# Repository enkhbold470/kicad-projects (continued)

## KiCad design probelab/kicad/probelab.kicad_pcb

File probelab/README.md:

# ProbeLab

An RP2040 USB-C logic analyzer: 16 buffered 5 V-tolerant inputs plus two low-speed scope channels.

| Layers | Size | Parts | Nets | Connections routed | Vias | ERC errors | DRC errors / unconnected / parity |
|---|---|---|---|---|---|---|---|
| 4 | 58 x 70 mm | 88 | 84 | 253 -> 0 open | 171 | 0 | 0 / 0 / 0 |

**Not fabricated, assembled or powered.** Every number on this page is measured by KiCad 10 on the files in this folder; the full measurements are in [`report.json`](report.json).

| | |
|---|---|
| KiCad project | [`kicad/`](kicad/) |
| Gerbers, BOM, CPL, STEP, schematic PDF | [`fab/`](fab/) |
| Renders | [top](media/top.png), [bottom](media/bottom.png) |
| Design process, every step as KiCad rendered it | [`media/design-process.mp4`](media/design-process.mp4) |

ProbeLab is a USB-C logic analyzer meant for sigrok/PulseView with sigrok-pico-style RP2040 firmware. It has 16 buffered and clamped logic inputs and two low-speed scope channels into the RP2040's own ADC, on a 58 x 70 mm, 4-layer board.

It was designed with the HeyPCB method on KiCad 10 (10.0.6), headless. A hand-written brief (`board.json`) is composed from reusable circuit blocks, and one pipeline run then does the schematic, ERC, a netlist round trip, placement, routing with Freerouting 2.4.1, pours and stitching, DRC with schematic parity, a fab gate, the fab outputs, 3D renders and a video. In the heypcb-kicad repository, `./run.sh --board boards/probelab` rebuilds all of it from `board.json`.

**Status: not fabricated, assembled or powered.** The final run passes every gate it has: ERC, the netlist round trip, routing to 0 open, DRC with schematic parity, DFM and the fab gate. That shows the design files agree with each other and with the fab's rules. It does not show that the circuit works.

**Limits.** The scope channels are low speed: they use the RP2040's ADC, 500 kS/s (datasheet) shared between the enabled channels. The logic inputs read 3.3 V and 5 V logic. 1.8 V logic sits below the buffer's 2.0 V VIH and will not read reliably.

**Firmware is separate.** Nothing here contains or tests firmware. The GPIO map below is what a firmware build has to match, and compatibility with sigrok-pico has not been checked on hardware.

## Files

| Path | Contents |
|---|---|
| `board.json` | the brief the pipeline built from |
| `report.json` | the run's measurements; every gate number below comes from it |
| `kicad/` | `probelab.kicad_pro`, `probelab.kicad_sch`, `probelab.kicad_pcb`. `models/` holds a simplified body for the USB-C receptacle, because KiCad 10 ships no 3D model for the HRO TYPE-C-31-M-12. It is not the vendor model |
| `fab/probelab_gerbers.zip` | 4 copper layers, mask, paste, silkscreen, outline, drill and drill map, gerber job |
| `fab/probelab_bom.csv` | 32 lines, 84 parts, each with an LCSC number |
| `fab/probelab_cpl_jlc.csv`, `fab/probelab_pos.csv` | placement for the 81 SMD parts (the through-hole headers are not in them) |
| `fab/probelab_schematic.pdf`, `fab/probelab.step` | schematic and 3D model |
| `media/` | board images and the run recorded stage by stage (`design-process.gif`, `design-process.mp4`) |

## Specs

- **MCU:** RP2040 with a 12 MHz Abracon ABM8-272-T3 crystal (CL 10 pF; 15 pF load caps, 1k on XOUT), the way Raspberry Pi's minimal design wires it.
- **Flash:** W25Q128JVSIQ, 16 MB, QSPI.
- **Core supply:** the RP2040's on-chip regulator makes the 1.1 V core (VREG_VOUT to both DVDD pins, 1 uF at each end of the regulator).
- **Decoupling:** 100 nF on every IOVDD, DVDD, USB_VDD and ADC_AVDD pin and 1 uF on VREG_VIN and VREG_VOUT, all 0402, all on the top side within 2.3 mm of the pin each one serves, each joined to it on F.Cu with no via (measured, see below).
- **USB:** USB-C receptacle (HRO TYPE-C-31-M-12) with 5.1k CC pull-downs, a USBLC6-2SC6 ESD clamp, and 27R in series with D+/D-.
- **Power:** AP2112K-3.3 LDO from VBUS. The draw is expected to stay well under 150 mA. That is an estimate; nothing has been powered.
- **Logic inputs (16, D0-D15):**
  - two 2x10 0.1" headers, signals on the even pins, ground on every odd pin and on pins 18/20;
  - each line clamped at the header by a USBLC6-4SC6 (rail pin on VBUS, so 5 V logic passes);
  - then 100R in series into an SN74LVC245A powered at 3.3 V, fixed A to B (DIR high, OE low), which drives GPIO2-GPIO17;
  - inputs are 5 V tolerant, with thresholds VIH 2.0 V / VIL 0.8 V.
- **Scope inputs (2):** a 1x4 header (CH1, GND, CH2, GND). Each channel has:
  - a PCM12 AC/DC slide switch shorting a 100 nF coupling cap (AC corner about 1.4 Hz);
  - 1M into a node held at mid-rail by 220k/220k, so Vnode = 0.099 x Vin + 1.49 V and about -15 V to +18 V spans 0-3.3 V, with about 1.1 Mohm input resistance;
  - a TLV9061 rail-to-rail buffer, then 47R + 1 nF into the ADC pin.
  - CH1 goes to ADC0 (GPIO26) and CH2 to ADC1 (GPIO27).
- **UI:** BOOT button (QSPI_SS through 1k), RESET button (RUN, 10k pull-up), and three LEDs: PWR (green, 3V3), STAT (GPIO25) and ACT (GPIO24).
- **Board:** 58 x 70 mm with 2 mm corner radii, 4 copper layers (below), every part on the top side. Four M3 holes, each 3.50 mm in from both edges at its corner: a 51 x 63 mm pattern centred on the board. 88 footprints: 84 populated parts and the 4 holes.
- **Silkscreen:** D0-D15 and the two all-ground rows of each header (pins 17-20) are named on both faces, CH1/GND/CH2/GND beside the scope header, BOOT, RST, USB, PWR, STAT and ACT beside their parts, DC and AC beside each switch's throws, and four title lines on the back (name, "16ch logic + 2ch scope", "RP2040 / sigrok", revision). The odd-pin grounds of the outer header column carry no label.

| Function | RP2040 pin(s) |
|---|---|
| D0-D7 (header J2, via U5) | GPIO2-GPIO9 |
| D8-D15 (header J3, via U8) | GPIO10-GPIO17 |
| Scope CH1 / CH2 | GPIO26 (ADC0) / GPIO27 (ADC1) |
| STAT / ACT LED | GPIO25 / GPIO24 |
| BOOT / RESET | QSPI_SS via 1k / RUN |
| Not connected | GPIO0-1, GPIO18-23, GPIO28-29, SWCLK, SWDIO |

## RP2040 decoupling, measured

Read off the final `kicad/probelab.kicad_pcb` with KiCad's Python (`pcbnew`). *Pad to pin* is the distance from the centre of the cap's supply pad (pad 1) to the centre of the RP2040 pin it serves. *Track path* is the shortest run of copper track between the two pads, through vias if any; the 3V3 pour on In1 is not counted. *Before* is the same measurement on the previous build of this board, with the caps where the earlier brief put them.

| Cap | Pin | Supply | Value | Pad to pin | Track path | Before |
|---|---|---|---|---|---|---|
| C1 | 1 | IOVDD | 100 nF | 1.51 mm | 1.61 mm, F.Cu | 1.51 mm, 1.61 mm F.Cu |
| C2 | 10 | IOVDD | 100 nF | 1.63 mm | 1.63 mm, F.Cu | 5.31 mm, 7.68 mm F.Cu |
| C3 | 22 | IOVDD | 100 nF | 1.35 mm | 1.11 mm, F.Cu | 4.89 mm, 13.31 mm F.Cu |
| C4 | 33 | IOVDD | 100 nF | 1.23 mm | 1.23 mm, F.Cu | 2.25 mm, 2.63 mm F.Cu |
| C5 | 42 | IOVDD | 100 nF | 1.23 mm | 1.23 mm, F.Cu | 2.25 mm, 2.63 mm F.Cu |
| C6 | 49 | IOVDD | 100 nF | 1.24 mm | 1.40 mm, F.Cu | 1.34 mm, 1.23 mm F.Cu |
| C7 | 48 | USB_VDD | 100 nF | 2.02 mm | 2.73 mm, F.Cu | 7.74 mm, 23.77 mm through 2 vias |
| C8 | 43 | ADC_AVDD | 100 nF | 2.07 mm | 3.57 mm, F.Cu | 2.16 mm, 2.68 mm F.Cu |
| C9 | 44 | VREG_VIN | 1 uF | 2.24 mm | 5.23 mm, F.Cu | 1.67 mm, 1.98 mm F.Cu |
| C10 | 45 | VREG_VOUT | 1 uF | 1.76 mm | 2.04 mm, F.Cu | 1.37 mm, 1.46 mm F.Cu |
| C11 | 23 | DVDD | 100 nF | 1.58 mm | 1.68 mm, F.Cu | 4.96 mm, 7.29 mm F.Cu |
| C12 | 50 | DVDD | 100 nF | 1.87 mm | 2.00 mm, F.Cu | 9.17 mm, 16.33 mm through 3 vias |

- No cap is on the bottom side, and no cap reaches its pin through a via. A track path can come out shorter than the centre distance, because it is counted from where the track meets each pad.
- The top edge of the QFN carries pins 48-50 between the QSPI pins and the USB pair. The flash is turned (rotation 270 in the brief) so no QSPI line crosses the space above them. C6 sits straight over pins 49 and 48 (both 3V3), C12 up and left of pin 50, C7 up and right of pin 48. The cost is on the right of the USB pair: C10 and C9 moved 0.9 and 0.8 mm right to leave a 1.05 mm channel for the USB lines, so they are 0.39 and 0.57 mm farther from pins 45 and 44 than before.
- **C9's path is long.** Its pad is 2.24 mm from pin 44, but the router joined pins 43/44 to pin 42's cap C5 and the corner cap C8 and reached C9 from C8, so the shortest track from C9 to pin 44 runs 5.23 mm. C8's 3.57 mm path also runs through pin 42 and C5. Two variants of the brief that moved C10 0.1 and 0.2 mm up gave C9 5.12 and 4.33 mm, but cost C1 a 45 mm path through 3 vias or C10 a path through 2 vias, so they were not kept.
- On the left side, C2 sits level with pin 10 in the middle of the GPIO escape. The router takes GPIO6-9 (pins 8, 9, 11 and 12) past it through vias, two of them under the QFN body.
- The bottom pins 22 and 23 have their caps directly under them (C3, C11), right of the XOUT line. R1, the 1k on XOUT, moved 0.3 mm down to make room.

## Stackup and copper

Read off the final `kicad/probelab.kicad_pcb` with KiCad's Python (`pcbnew`); the track lengths and via counts match `report.json`.

| Layer | While routing | After routing | Tracks | Pour fill |
|---|---|---|---|---|
| F.Cu | signal | GND pour | 874.6 mm | 3023 mm² |
| In1.Cu | signal | 3V3 pour | 630.1 mm | 3194 mm² |
| In2.Cu | GND plane (a Specctra power layer, no tracks) | GND pour | none | 3630 mm² |
| B.Cu | signal | GND pour | 290.1 mm | 3440 mm² |

- `board.json` sets one plane, `In2.Cu: GND`. The brief has no `pours` key, so the 3V3 pour on In1 comes from the pipeline's 4-layer pour rule: when no plane carries a supply, the inner signal layer takes the dominant rail after routing. It covers In1's 3V3 tracks.
- 920 tracks, 1794.8 mm. VBUS is 0.4 mm except 6 segments (5.5 mm) at 0.3 mm. 72 segments (57.0 mm in all) are 0.15 mm: short pad exits from Freerouting's fanout solve on 33 nets, which the width floor could not widen without breaking a clearance. Every other track is 0.2 mm, including 3V3, 1V1 and USB D+/D-.
- 171 vias, all through vias of 0.6 mm with a 0.3 mm hole: 114 from routing and 57 GND stitching vias (the stitcher placed 63; the silk stage removed 6 under text).
- 10 of the routing vias sit under the RP2040's body, inside its ring of pins (6 on the previous build).
- `board.keepouts` holds one rule area, `pin_labels_D10_D15`: no vias on any layer in a 3 x 14.5 mm strip under the D10-D15 header labels.
- The gerber job gives four 35 µm copper layers, three 0.48 mm FR4 dielectrics, 1.6 mm overall. That is KiCad's default 4-layer stackup, not a fab's. Nothing on the board is impedance controlled.

## Choices and substitutions

- **The RP2040's own ADC instead of a fast external ADC.** The RP2040 has 30 GPIO, and 16 of them go to the logic inputs.
  - AD9288 (dual 8-bit) has no KiCad 10 symbol.
  - ADC08060 has a symbol, but it is one channel with 8 parallel data lines. Two of them need 16 data pins plus a clock, which does not fit beside 16 logic channels.
  - Two analog nets into GPIO26/27 is by far the most routable option. GPIO26-29 are the RP2040's only ADC pins, so any RP2040 capture firmware reads analog there.
  - The cost: RP2040 ADC bandwidth. Its 500 kS/s (datasheet) is shared between the enabled channels.
- **TLV9061 instead of AD8065 or OPA356.**
  - AD8065 has no KiCad 10 symbol and needs a supply above 3.3 V.
  - OPA356 has a symbol, but it is rail-to-rail on its output only. Its input range stops short of V+, so at 3.3 V it would clip a node biased to mid-rail.
  - TLV9061 is a single-channel SOT-23-5, rail to rail on input and output, 10 MHz, and in stock (C398358).
- **SN74LVC245A, not 74LVC8T245.** It needs one supply and no target-voltage selector. The trade-off: it reads 3.3 V and 5 V logic, but not 1.8 V logic reliably.
- **ABM8-272-T3 (Extended) instead of the Basic C9002 crystal.** C9002 is CL 20 pF. ABM8-272-T3 (CL 10 pF) is the crystal Raspberry Pi's minimal design uses, and 15 pF caps suit it.
- **GND plane on In2, not In1.** Measured on 2026-09-30, on the earlier 56 x 68 mm outline: with In1 as the Specctra power layer, Freerouting left the header ground pins open in every solve (23, 30 and 37 opens, all GND at J2/J3). With In2 as the power layer it closed them. That was before the pipeline started removing plane-layer shapes from through-hole pin padstacks for the router, a change aimed at the same kind of failure. In1 as the plane has not been re-tested since.
- **58 x 70 mm, not 56 x 68.** Once the router was held to the brief's 0.5 mm hole-to-hole spacing between vias, the 56 x 68 mm board left 1V1 open at U1 pin 50 (measured 2026-10-01). At 58 x 70 mm it routed to 0 open.
- **PWR class is VBUS only (0.4 mm).** 3V3 and 1V1 stay at the 0.2 mm default. A 0.3 mm class could not enter the RP2040's 0.2 mm QFN power pins with neckdown off (6 opens until the ladder narrowed it, measured 2026-09-30).
- **QFN-56 ThermalVias footprint.** The exposed pad is the RP2040's only ground pin. The plain footprint leaves it enclosed by 0.4 mm-pitch pins. The symbol's footprint filter allows this variant.
- **Every RP2040 passive is locked in the brief,** and the flash is its own block. Left to the shelf placer, every IOVDD cap landed around the flash (it prefers the IC with fewer pads on the rail). The locks put each supply cap beside its pin with pad 1 toward it. The USB channel between C7 and C10 is 1.05 mm. At 0.9 mm, the bare minimum for two 0.2 mm tracks, the first run of this placement routed every connection, but once the label keep-out was added the fanout solve left U1_DM_MCU open; at 1.05 mm it routes everything (measured 2026-10-01, one run each). Since the keep-out, the fanout-off solve has left VBUS (U7.5 to C16.1) open on every run.
- **The input clamps sit 1.8 mm farther from the headers than before** (pads from 10.0 mm), so the pin labels the silk stage sets inside each signal pad fit on the front. A via-free strip (`board.keepouts`) under the D10-D15 labels keeps router vias off them; without it, two router vias left D10 and D14 unlabelled on both faces.
- **The coupling cap of each scope channel is locked between its switch's input and common rows,** clear of the DC and AC words beside pads 1 and 3. Placed by the shelf placer, it sat where the DC word goes.

New blocks, all prefixed `probe_`:
- `probe_rp2040_core`
- `probe_qspi_flash`
- `probe_logic_bank8`
- `probe_scope_frontend`
- `probe_header_1x04`
- `probe_mounting_holes_m3`

Reused blocks:
- `usb_c_data_5v`
- `usb_esd_usblc6`
- `lipo_ldo_ap2112k` (VBAT renamed onto VBUS)
- `tactile_button`
- `led_indicator`
- `gpio_led`

## Measured gates

The final run, 2026-10-01, with media. Every number is from `report.json`, except the block counts, which are counted in `board.json`.

| Gate | Result |
|---|---|
| Composition | 16 block instances, 12 distinct blocks: 88 parts, 84 nets, 16 no-connect pins |
| Part binding | 84 of 84 populated parts bound to LCSC numbers; the 4 mounting holes are DNP and not in the BOM. 0 unsourced, 0 identity conflicts. 14 distinct Extended parts, about $42 in JLC loading fees |
| ERC (`--severity-all`) | 0 errors, 0 warnings |
| Netlist round trip | identical, 84 nets |
| Placement | 44 parts locked by the brief, 3 edge parts (USB-C, both AC/DC switches), 3 LED-block anchors at brief targets, 38 placed by the shelf placer around the pins they serve |
| Routing | 253 connections, two rung-1 Freerouting solves. **Fanout on: 0 open** in 20.0 s with 114 vias. This solve is kept. Fanout off: 1 open (VBUS, U7.5 to C16.1) in 47.4 s with 78 vias; the last-mile router found no path for it |
| Copper | 920 tracks, 1794.8 mm (F.Cu 874.6, In1.Cu 630.1, B.Cu 290.1) |
| Pours (after a measured 0 open) | GND on F.Cu, B.Cu and In2.Cu, 3V3 on In1.Cu. 63 stitching vias placed, 177 vias in all before the silk stage. 0 open after the pours, after stitching and at the end |
| DRC (`--severity-all --schematic-parity`) | fresh: 0 errors, 0 unconnected, **0 parity issues**, 4 warnings: 3 `lib_footprint_mismatch`, 1 `hole_to_hole` |
| DFM (`jlcpcb_4layer`) | 0 errors, 1 warning: 262 stock-footprint silk strokes at 0.12 mm, which the fab prints at its 0.15 mm minimum |
| Fab gate | **ready**, no blockers. 4 copper gerbers and a gerber job with LayerNumber 4, drill, BOM, CPL (11 rotations corrected), position file, schematic PDF, STEP |
| Silkscreen | 48 header pin labels, 10 words, 57 designators seated, 23 hidden, 13 footprint silk items clipped at the board edge, 4 of 4 back-side title lines placed (as one block, 10 mm left of the brief's spot), 6 stitching vias removed under text |
| Media | 63 3D frames, the raytraced renders and the design-process video all ran; the video is 219 stills at 1920 x 1080, 30 fps, 149.2 s long (measured with ffprobe) |

- **The 3 `lib_footprint_mismatch` warnings** are J1 (USB-C) and SW1/SW2 (PCM12). The silkscreen stage removed the footprint silk that ran past or within 0.3 mm of the board edge: compared with KiCad's library footprints, J1 went from 5 silk items to 2 and each switch from 10 to 5. Those are the 13 clipped items, and they are why the footprints no longer match the library copies.
- **The `hole_to_hole` warning** is a USB_DM via at (42.27, 13.05) and a VBUS via at (42.42, 12.30) mm from the board origin, between the ESD clamp and the LDO: 0.47 mm hole to hole, under the brief's 0.5 mm. The project rates it a warning, so the gate passes; see the check list.
- The project's DRC settings exclude five checks: missing courtyard, track end not centred on a via, footprint filter mismatch, footprint type mismatch, and tuning-profile track geometry.

## Check these before ordering

- **It has never been built.** Nothing here has been fabricated, assembled or powered. Bring up one board rail by rail (VBUS, 3.3 V, the 1.1 V core) before trusting anything else.
- **Stackup.** Replace KiCad's default 4-layer stackup with the fab's own.
- **Logic levels.**
  - The LVC245A at 3.3 V reads 3.3 V and 5 V logic.
  - 1.8 V logic sits below its 2.0 V VIH.
  - Inputs have no pull-downs, so open probes read noise.
- **Back-feeding.** The input clamps' rail pins sit on VBUS. Probing a powered target with the analyzer unplugged can back-feed VBUS through the clamps' steering diodes. Plug in USB first.
- **Analog range and safety.**
  - About -15 V to +18 V (DC coupled), with about 1.1 Mohm input resistance. These are calculated from the values, not measured.
  - Gain and offset depend on 1% resistors, so calibrate in firmware.
  - The 1M is a 0603 rated 75 V, and the coupling cap is 50 V. There is no isolation from the USB host's ground. Do not probe mains.
- **AC/DC lever direction.** Each switch has DC printed beside pad 1, the throw on the input net (common pad 2 to pad 1 shorts the coupling cap), and AC beside pad 3, the unconnected throw, each level with its pad and 2.32 mm to the left of it. Which lever position joins pad 2 to pad 1 has not been checked against the C&K PCM12 datasheet. Check it before trusting the words.
- **Hole spacing.** One pair of vias near the ESD clamp is 0.47 mm hole to hole (DRC warning above). Check it against the fab's minimum hole spacing, or move one via in KiCad.
- **C9's track.** VREG_VIN's 1 uF is 2.24 mm from pin 44 but reaches it by 5.23 mm of track (see the decoupling table). Shorten it in KiCad if the regulator input matters to you.
- **Vias in the RP2040's exposed pad.** The ThermalVias footprint puts four 0.2 mm vias in the exposed pad. They are open holes: order them filled and capped, or expect solder to wick into them.
- **Through-hole headers.** J2, J3 (2x10) and J4 (1x4) are in the BOM but not in the CPL or the position file. Solder them by hand or order through-hole assembly.
- **No debug header.** SWD (SWCLK/SWDIO) and the UART pins (GPIO0/1) are not broken out. Flashing is over USB with BOOT held.
- **USB.** D+/D- are 0.2 mm tracks with no impedance control, and not a coupled pair. D+ runs 10.8 mm from the RP2040 to its 27R through 3 vias (F.Cu, In1, B.Cu, leaving pin 47 under the QFN body) and 33.2 mm on F.Cu from there to the receptacle; D- runs 6.4 mm on F.Cu to its 27R and 27.4 mm through 2 vias (F.Cu, In1) from there. The 10.2 mm length difference is about 0.07 ns, against Full Speed's 83 ns bit time; check it if the board ever moves to a faster interface.
- **Part numbers.**
  - All 84 populated parts are bound to LCSC numbers from heypcb-kicad's pinned parts table. The rows added for this board were read on 2026-09-30 through `heypcb parts search/lookup` (the jlcsearch.tscircuit.com mirror). That mirror carries no manufacturer names.
  - Stock in the table, with its snapshot date: the crystal (C20625731) 18110 on 2026-09-30, the PCM12 switch (C221841) 2789 on 2026-06-25, the PTS810 button (C116501) 1744 on 2026-06-23.
  - Stock and Basic/Extended class go stale. Re-check them on jlcpcb.com.
- **Firmware pin map.** Build the firmware for D0-D15 = GPIO2-17 and the analog channels on GPIO26/27. That this matches a given sigrok-pico release has not been verified.

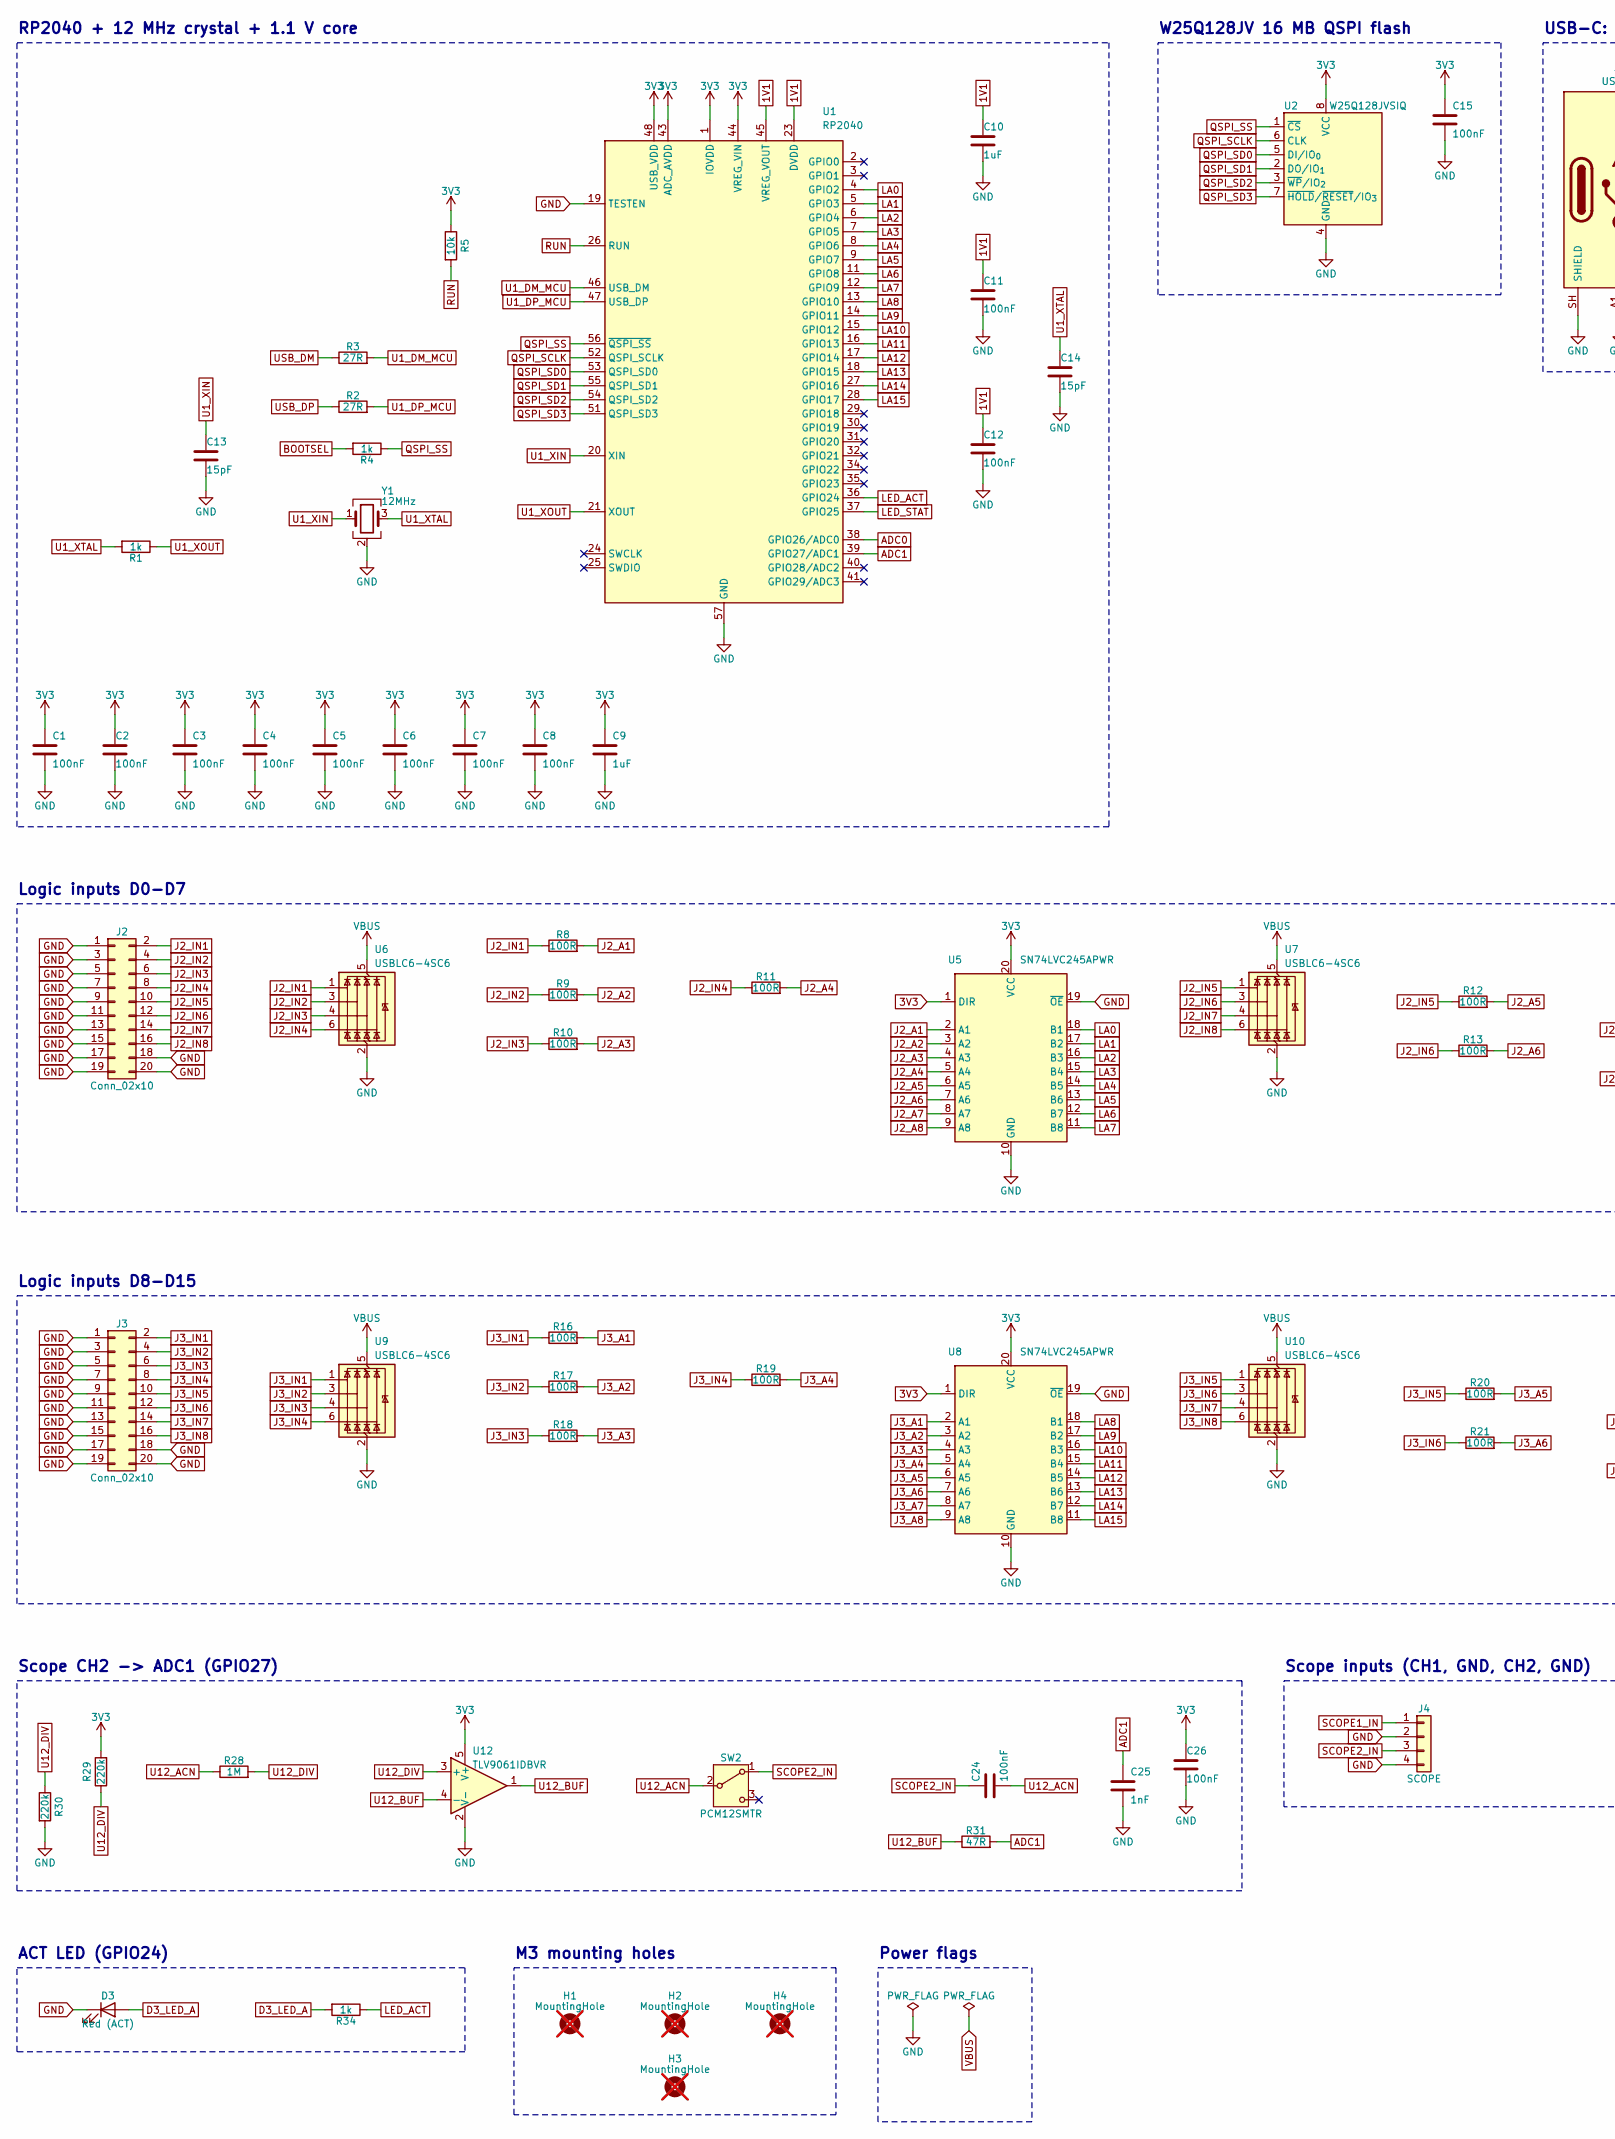
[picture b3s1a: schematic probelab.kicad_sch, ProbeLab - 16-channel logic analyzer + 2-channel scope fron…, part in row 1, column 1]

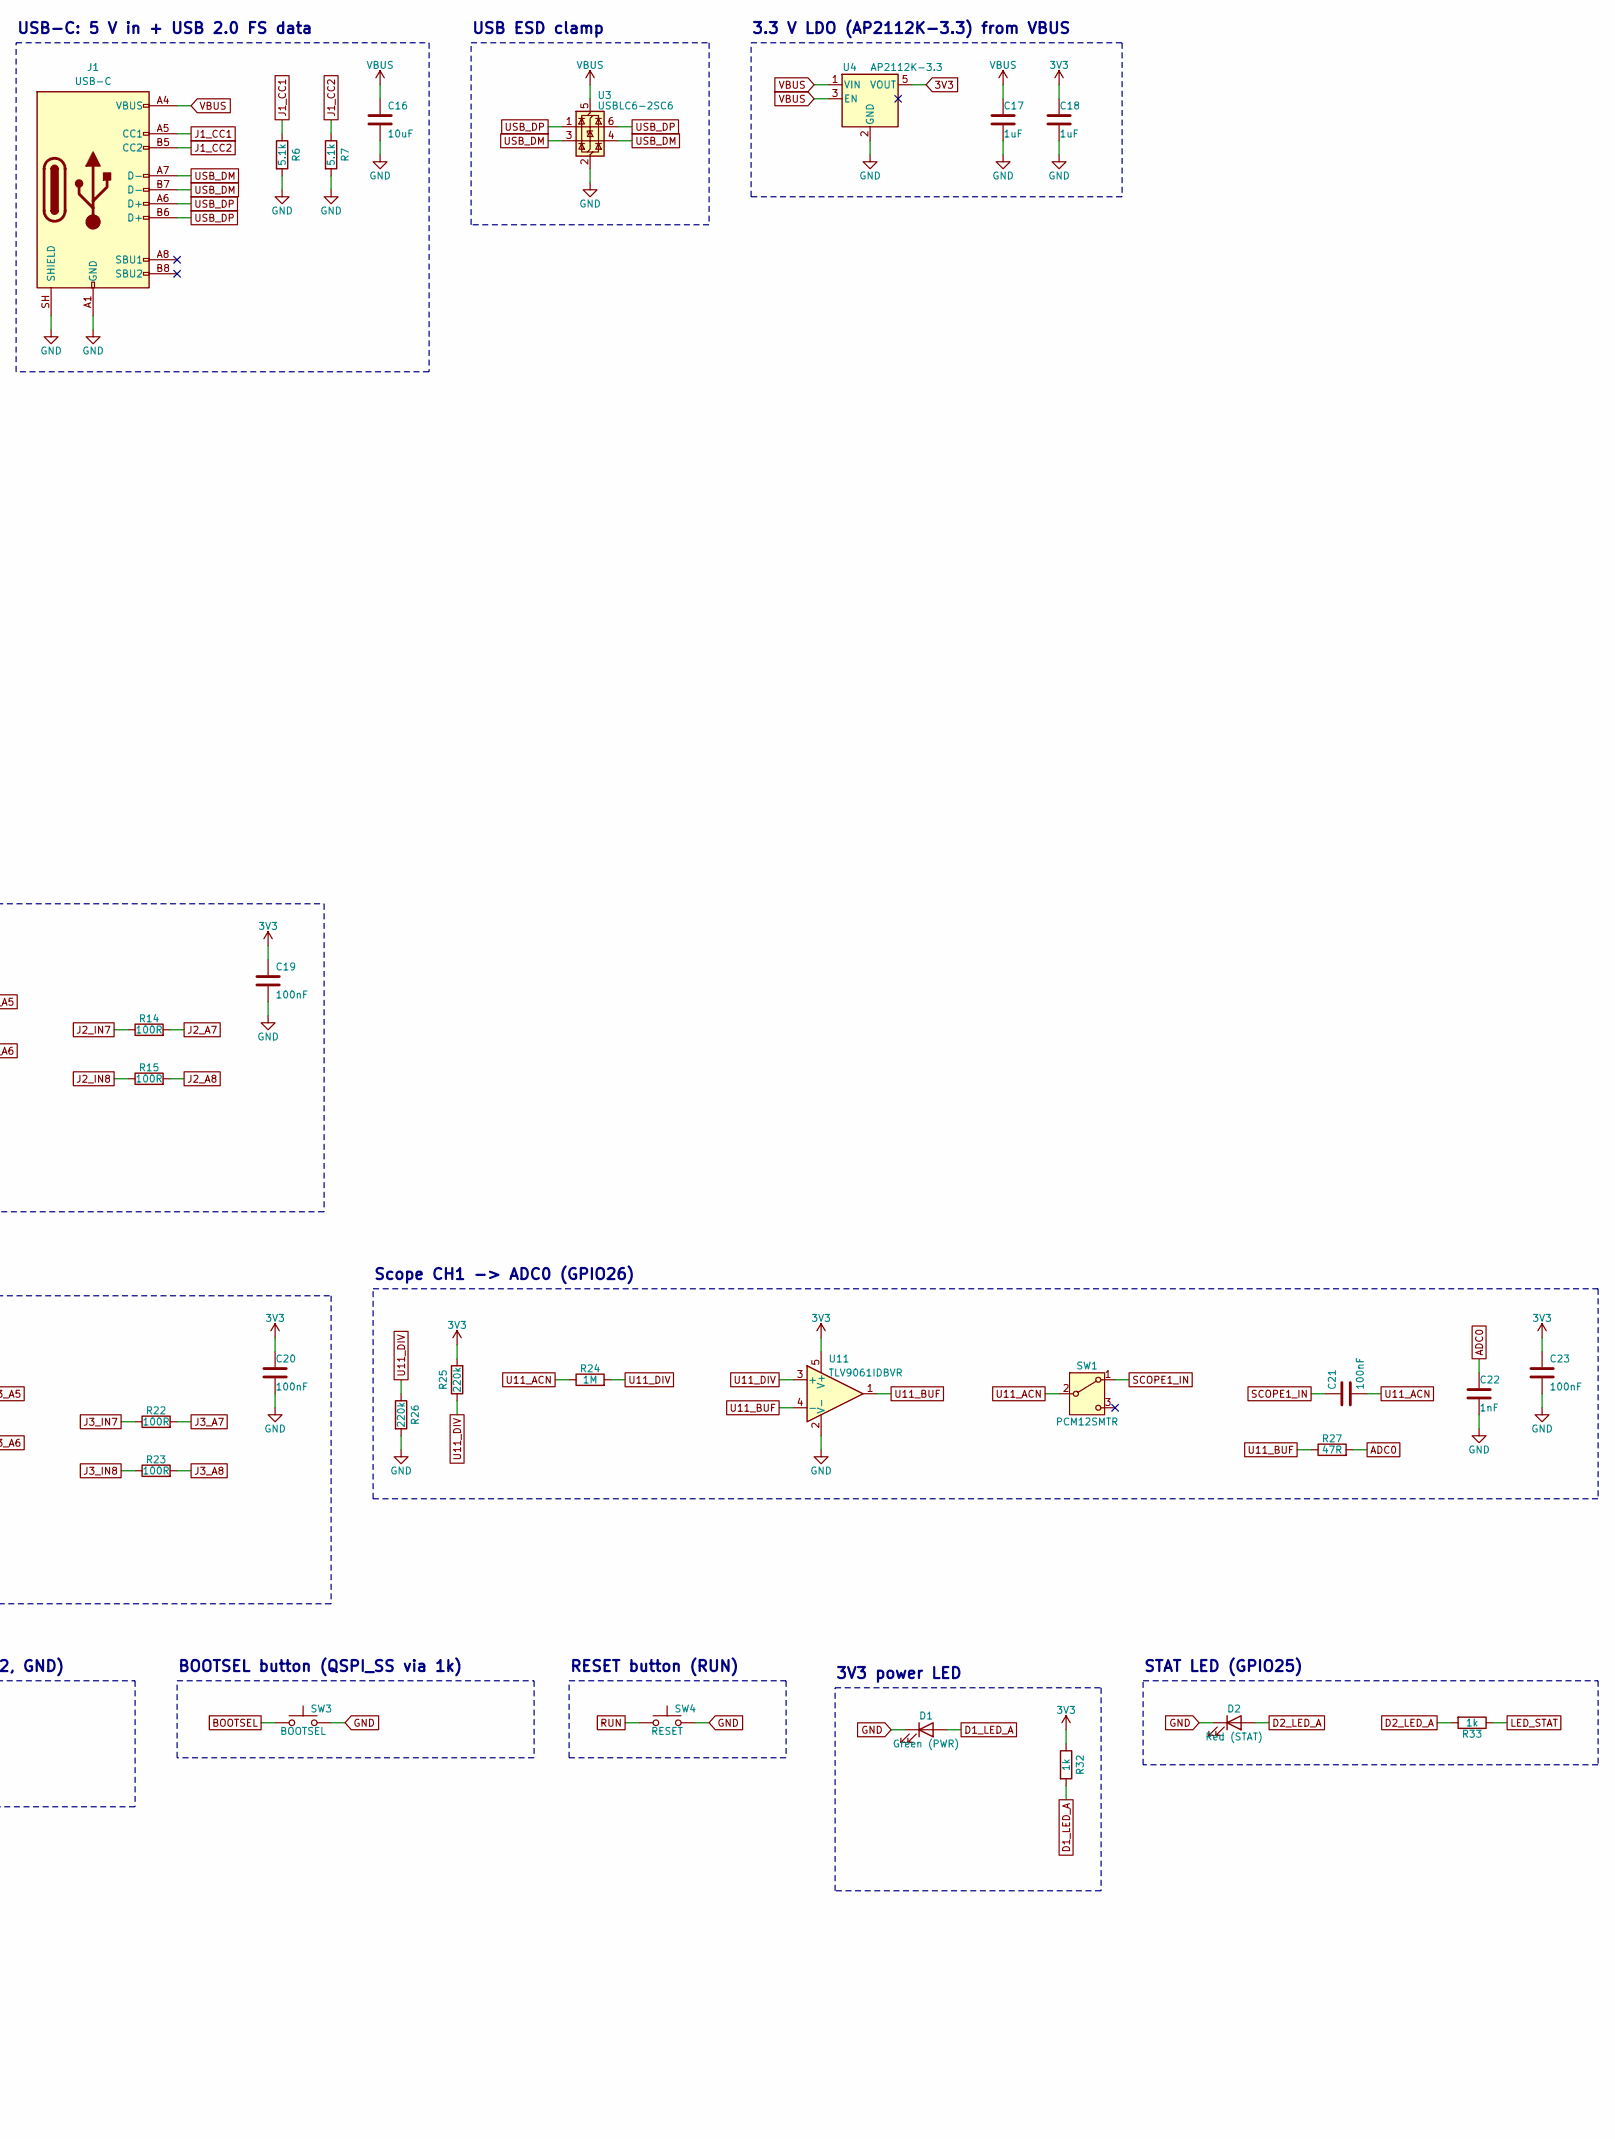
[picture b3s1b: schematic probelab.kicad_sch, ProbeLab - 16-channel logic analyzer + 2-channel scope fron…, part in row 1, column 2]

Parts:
C1, C2, C3, C4, C5, C6, C7, C8, C11, C12, C15: 100nF; C_0402_1005Metric; MPN CL05B104KO5NNNC; LCSC C1525
C9, C10: 1uF; C_0402_1005Metric; MPN CL05A105KA5NQNC; LCSC C52923
C13, C14: 15pF; C_0402_1005Metric; MPN 0402CG150J500NT; LCSC C1548
C16: 10uF; C_0805_2012Metric; MPN CL21A106KAYNNNE; LCSC C15850
C17, C18: 1uF; C_0603_1608Metric; MPN CL10A105KB8NNNC; LCSC C15849
C19, C20, C21, C23, C24, C26: 100nF; C_0603_1608Metric; MPN CC0603KRX7R9BB104; LCSC C14663
C22, C25: 1nF; C_0603_1608Metric; MPN CL10B102KB8NNNC; LCSC C1588
D1: Green (PWR); LED_0603_1608Metric; MPN KT-0603G; LCSC C12624
D2: Red (STAT); LED_0603_1608Metric; MPN KT-0603R; LCSC C2286
D3: Red (ACT); LED_0603_1608Metric; MPN KT-0603R; LCSC C2286
H1, H2, H3, H4: MountingHole; MountingHole_3.2mm_M3; not fitted
J1: USB-C; USB_C_Receptacle_HRO_TYPE-C-31-M-12; MPN TYPE-C-31-M-12; LCSC C165948
J2, J3: Conn_02x10; PinHeader_2x10_P2.54mm_Vertical; MPN PZ254V-12-20P; LCSC C492427
J4: SCOPE; PinHeader_1x04_P2.54mm_Vertical; MPN PZ254V-11-04P; LCSC C2691448
R1, R4, R32, R33, R34: 1k; R_0603_1608Metric; MPN 0603WAF1001T5E; LCSC C21190
R2, R3: 27R; R_0603_1608Metric; MPN 0603WAF270JT5E; LCSC C25190
R5: 10k; R_0402_1005Metric; MPN 0402WGF1002TCE; LCSC C25744
R6, R7: 5.1k; R_0402_1005Metric; MPN 0402WGF5101TCE; LCSC C25905
R8, R9, R10, R11, R12, R13, R14, R15, R16, R17, R18, R19, R20, R21, R22, R23: 100R; R_0402_1005Metric; MPN 0402WGF1000TCE; LCSC C25076
R24, R28: 1M; R_0603_1608Metric; MPN 0603WAF1004T5E; LCSC C22935
R25, R26, R29, R30: 220k; R_0603_1608Metric; MPN 0603WAF2203T5E; LCSC C22961
R27, R31: 47R; R_0603_1608Metric; MPN 0603WAF470JT5E; LCSC C23182
SW1, SW2: PCM12SMTR; SW_SPDT_PCM12; MPN PCM12SMTR; LCSC C221841
SW3: BOOTSEL; SW_SPST_PTS810; MPN PTS810SJM250SMTRLFS; LCSC C116501
SW4: RESET; SW_SPST_PTS810; MPN PTS810SJM250SMTRLFS; LCSC C116501
U1: RP2040; QFN-56-1EP_7x7mm_P0.4mm_EP3.2x3.2mm_ThermalVias; MPN RP2040; LCSC C2040
U2: W25Q128JVSIQ; SOIC-8_5.3x5.3mm_P1.27mm; MPN W25Q128JVSIQ; LCSC C97521
U3: USBLC6-2SC6; SOT-23-6; MPN USBLC6-2SC6; LCSC C7519
U4: AP2112K-3.3; SOT-23-5; MPN AP2112K-3.3TRG1; LCSC C51118
U5, U8: SN74LVC245APWR; TSSOP-20_4.4x6.5mm_P0.65mm; MPN SN74LVC245APWR; LCSC C7848
U6, U7, U9, U10: USBLC6-4SC6; SOT-23-6; MPN USBLC6-4SC6; LCSC C111212
U11, U12: TLV9061IDBVR; SOT-23-5; MPN TLV9061IDBVR; LCSC C398358
Y1: 12MHz; Crystal_SMD_3225-4Pin_3.2x2.5mm; MPN ABM8-272-T3; LCSC C20625731

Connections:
1V1: C10.1, C11.1, C12.1, U1.23 (DVDD), U1.45 (VREG_VOUT), U1.50 (DVDD)
3V3: C1.1, C2.1, C3.1, C4.1, C5.1, C6.1, C7.1, C8.1, C9.1, C15.1, C18.1, C19.1, C20.1, C23.1, C26.1, R5.1, R25.2, R29.2, R32.1, U1.1 (IOVDD), U1.10 (IOVDD), U1.22 (IOVDD), U1.33 (IOVDD), U1.42 (IOVDD), U1.43 (ADC_AVDD), U1.44 (VREG_VIN), U1.48 (USB_VDD), U1.49 (IOVDD), U2.8 (VCC), U4.5 (VOUT), U5.1 (DIR), U5.20 (VCC), U8.1 (DIR), U8.20 (VCC), U11.5 (V+), U12.5 (V+)
ADC0: C22.1, R27.2, U1.38 (GPIO26/ADC0)
ADC1: C25.1, R31.2, U1.39 (GPIO27/ADC1)
BOOTSEL: R4.2, SW3.1
D1_LED_A: D1.2 (A), R32.2
D2_LED_A: D2.2 (A), R33.2
D3_LED_A: D3.2 (A), R34.2
GND: C1.2, C2.2, C3.2, C4.2, C5.2, C6.2, C7.2, C8.2, C9.2, C10.2, C11.2, C12.2, C13.2, C14.2, C15.2, C16.2, C17.2, C18.2, C19.2, C20.2, C22.2, C23.2, C25.2, C26.2, D1.1 (K), D2.1 (K), D3.1 (K), J1.A1 (GND), J1.A12 (GND), J1.B1 (GND), J1.B12 (GND), J1.SH (SHIELD), J2.1, J2.3, J2.5, J2.7, J2.9, J2.11, J2.13, J2.15, J2.17, J2.18, J2.19, J2.20, J3.1, J3.3, J3.5, J3.7, J3.9, J3.11, J3.13, J3.15, J3.17, J3.18, J3.19, J3.20, J4.2, J4.4, R6.2, R7.2, R26.2, R30.2, SW3.2, SW4.2, U1.19 (TESTEN), U1.57 (GND), U2.4 (GND), U3.2 (GND), U4.2 (GND), U5.10 (GND), U5.19 (~OE), U6.2 (GND), U7.2 (GND), U8.10 (GND), U8.19 (~OE), U9.2 (GND), U10.2 (GND), U11.2 (V-), U12.2 (V-), Y1.2 (G), Y1.4 (G)
J1_CC1: J1.A5 (CC1), R6.1
J1_CC2: J1.B5 (CC2), R7.1
J2_A1: R8.2, U5.2 (A1)
J2_A2: R9.2, U5.3 (A2)
J2_A3: R10.2, U5.4 (A3)
J2_A4: R11.2, U5.5 (A4)
J2_A5: R12.2, U5.6 (A5)
J2_A6: R13.2, U5.7 (A6)
J2_A7: R14.2, U5.8 (A7)
J2_A8: R15.2, U5.9 (A8)
J2_IN1: J2.2, R8.1, U6.1 (I/O1)
J2_IN2: J2.4, R9.1, U6.3 (I/O2)
J2_IN3: J2.6, R10.1, U6.4 (I/O3)
J2_IN4: J2.8, R11.1, U6.6 (I/O4)
J2_IN5: J2.10, R12.1, U7.1 (I/O1)
J2_IN6: J2.12, R13.1, U7.3 (I/O2)
J2_IN7: J2.14, R14.1, U7.4 (I/O3)
J2_IN8: J2.16, R15.1, U7.6 (I/O4)
J3_A1: R16.2, U8.2 (A1)
J3_A2: R17.2, U8.3 (A2)
J3_A3: R18.2, U8.4 (A3)
J3_A4: R19.2, U8.5 (A4)
J3_A5: R20.2, U8.6 (A5)
J3_A6: R21.2, U8.7 (A6)
J3_A7: R22.2, U8.8 (A7)
J3_A8: R23.2, U8.9 (A8)
J3_IN1: J3.2, R16.1, U9.1 (I/O1)
J3_IN2: J3.4, R17.1, U9.3 (I/O2)
J3_IN3: J3.6, R18.1, U9.4 (I/O3)
J3_IN4: J3.8, R19.1, U9.6 (I/O4)
J3_IN5: J3.10, R20.1, U10.1 (I/O1)
J3_IN6: J3.12, R21.1, U10.3 (I/O2)
J3_IN7: J3.14, R22.1, U10.4 (I/O3)
J3_IN8: J3.16, R23.1, U10.6 (I/O4)
LA0: U1.4 (GPIO2), U5.18 (B1)
LA1: U1.5 (GPIO3), U5.17 (B2)
LA2: U1.6 (GPIO4), U5.16 (B3)
LA3: U1.7 (GPIO5), U5.15 (B4)
LA4: U1.8 (GPIO6), U5.14 (B5)
LA5: U1.9 (GPIO7), U5.13 (B6)
LA6: U1.11 (GPIO8), U5.12 (B7)
LA7: U1.12 (GPIO9), U5.11 (B8)
LA8: U1.13 (GPIO10), U8.18 (B1)
LA9: U1.14 (GPIO11), U8.17 (B2)
LA10: U1.15 (GPIO12), U8.16 (B3)
LA11: U1.16 (GPIO13), U8.15 (B4)
LA12: U1.17 (GPIO14), U8.14 (B5)
LA13: U1.18 (GPIO15), U8.13 (B6)
LA14: U1.27 (GPIO16), U8.12 (B7)
LA15: U1.28 (GPIO17), U8.11 (B8)
LED_ACT: R34.1, U1.36 (GPIO24)
LED_STAT: R33.1, U1.37 (GPIO25)
QSPI_SCLK: U1.52 (QSPI_SCLK), U2.6 (CLK)
QSPI_SD0: U1.53 (QSPI_SD0), U2.5 (DI/IO_{0})
QSPI_SD1: U1.55 (QSPI_SD1), U2.2 (DO/IO_{1})
QSPI_SD2: U1.54 (QSPI_SD2), U2.3 (~WP/IO_{2})
QSPI_SD3: U1.51 (QSPI_SD3), U2.7 (~HOLD/~RESET/IO_{3})
QSPI_SS: R4.1, U1.56 (~QSPI_SS), U2.1 (~CS)
RUN: R5.2, SW4.1, U1.26 (RUN)
SCOPE1_IN: C21.1, J4.1, SW1.1 (A)
SCOPE2_IN: C24.1, J4.3, SW2.1 (A)
U1_DM_MCU: R3.2, U1.46 (USB_DM)
U1_DP_MCU: R2.2, U1.47 (USB_DP)
U1_XIN: C13.1, U1.20 (XIN), Y1.1
U1_XOUT: R1.1, U1.21 (XOUT)
U1_XTAL: C14.1, R1.2, Y1.3
U11_ACN: C21.2, R24.1, SW1.2 (B)
U11_BUF: R27.1, U11.1, U11.4 (-)
U11_DIV: R24.2, R25.1, R26.1, U11.3 (+)
U12_ACN: C24.2, R28.1, SW2.2 (B)
U12_BUF: R31.1, U12.1, U12.4 (-)
U12_DIV: R28.2, R29.1, R30.1, U12.3 (+)
USB_DM: J1.A7 (D-), J1.B7 (D-), R3.1, U3.3 (I/O2), U3.4 (I/O2)
USB_DP: J1.A6 (D+), J1.B6 (D+), R2.1, U3.1 (I/O1), U3.6 (I/O1)
VBUS: C16.1, C17.1, J1.A4 (VBUS), J1.A9 (VBUS), J1.B4 (VBUS), J1.B9 (VBUS), U3.5 (VBUS), U4.1 (VIN), U4.3 (EN), U6.5 (VBUS), U7.5 (VBUS), U9.5 (VBUS), U10.5 (VBUS)

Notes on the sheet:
RP2040 + 12 MHz crystal + 1.1 V core
W25Q128JV 16 MB QSPI flash
USB-C: 5 V in + USB 2.0 FS data
USB ESD clamp
3.3 V LDO (AP2112K-3.3) from VBUS
Logic inputs D0-D7
Logic inputs D8-D15
Scope CH1 -> ADC0 (GPIO26)
Scope CH2 -> ADC1 (GPIO27)
Scope inputs (CH1, GND, CH2, GND)
BOOTSEL button (QSPI_SS via 1k)
RESET button (RUN)
3V3 power LED
STAT LED (GPIO25)
ACT LED (GPIO24)
M3 mounting holes
Power flags

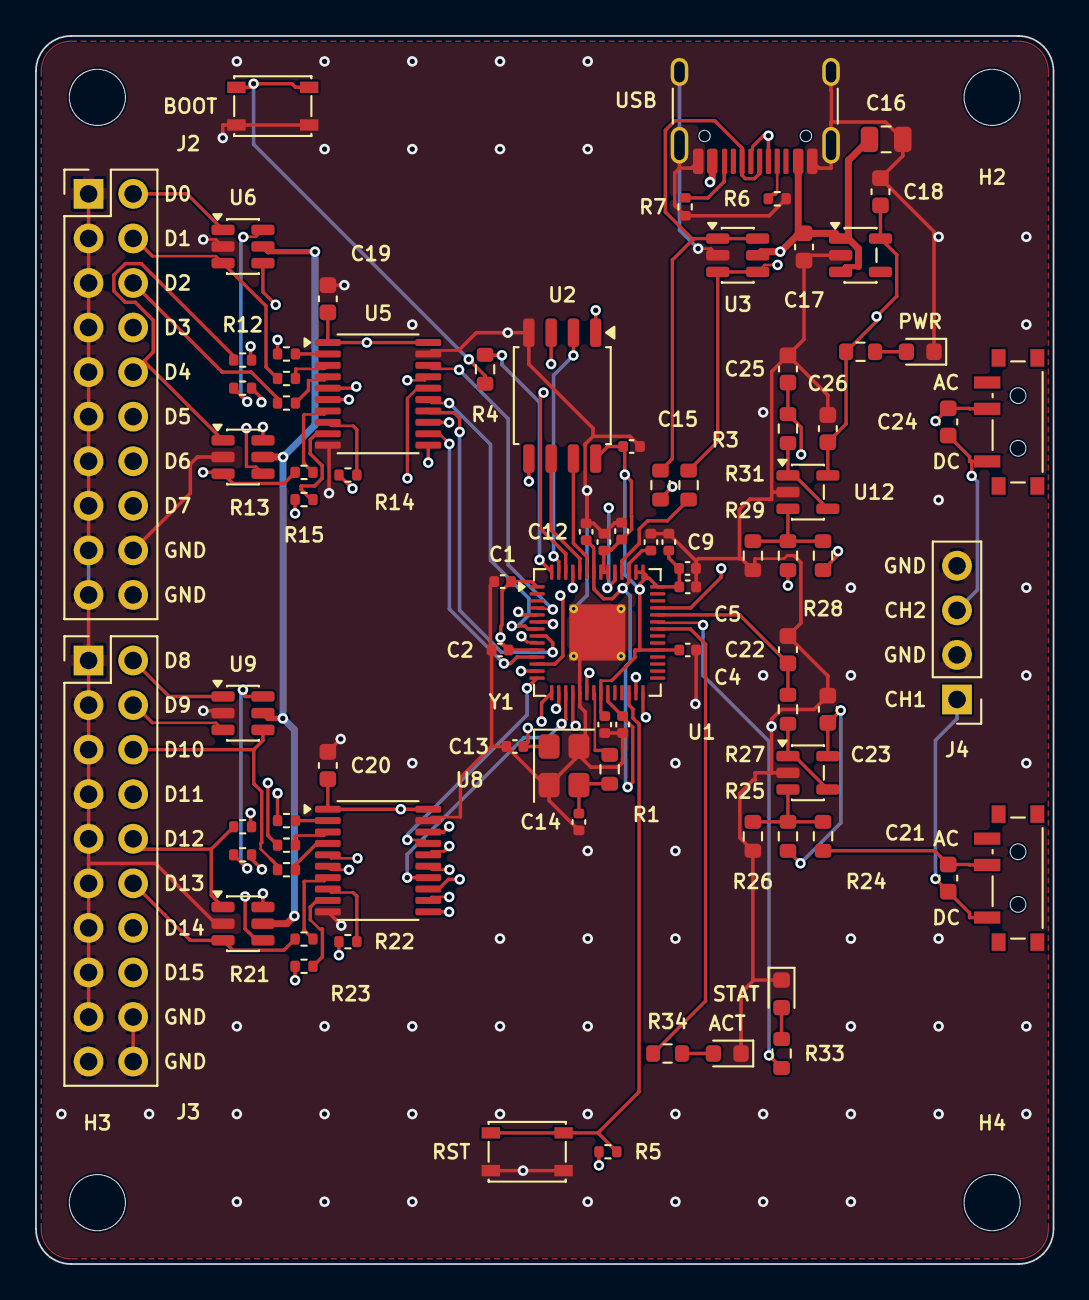
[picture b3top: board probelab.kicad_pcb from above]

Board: 4 copper layers, 58.0 x 70.0 mm, 88 parts (0 on the bottom side), 84 nets.

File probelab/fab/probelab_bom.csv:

"Reference","Value","Footprint","MPN","LCSC","Qty"
"C1,C2,C3,C4,C5,C6,C7,C8,C11,C12,C15","100nF","Capacitor_SMD:C_0402_1005Metric","CL05B104KO5NNNC","C1525","11"
"C9,C10","1uF","Capacitor_SMD:C_0402_1005Metric","CL05A105KA5NQNC","C52923","2"
"C13,C14","15pF","Capacitor_SMD:C_0402_1005Metric","0402CG150J500NT","C1548","2"
"C16","10uF","Capacitor_SMD:C_0805_2012Metric","CL21A106KAYNNNE","C15850","1"
"C17,C18","1uF","Capacitor_SMD:C_0603_1608Metric","CL10A105KB8NNNC","C15849","2"
"C19,C20,C21,C23,C24,C26","100nF","Capacitor_SMD:C_0603_1608Metric","CC0603KRX7R9BB104","C14663","6"
"C22,C25","1nF","Capacitor_SMD:C_0603_1608Metric","CL10B102KB8NNNC","C1588","2"
"D1","Green (PWR)","LED_SMD:LED_0603_1608Metric","KT-0603G","C12624","1"
"D2","Red (STAT)","LED_SMD:LED_0603_1608Metric","KT-0603R","C2286","1"
"D3","Red (ACT)","LED_SMD:LED_0603_1608Metric","KT-0603R","C2286","1"
"J1","USB-C","Connector_USB:USB_C_Receptacle_HRO_TYPE-C-31-M-12","TYPE-C-31-M-12","C165948","1"
"J2,J3","Conn_02x10","Connector_PinHeader_2.54mm:PinHeader_2x10_P2.54mm_Vertical","PZ254V-12-20P","C492427","2"
"J4","SCOPE","Connector_PinHeader_2.54mm:PinHeader_1x04_P2.54mm_Vertical","PZ254V-11-04P","C2691448","1"
"R1,R4,R32,R33,R34","1k","Resistor_SMD:R_0603_1608Metric","0603WAF1001T5E","C21190","5"
"R2,R3","27R","Resistor_SMD:R_0603_1608Metric","0603WAF270JT5E","C25190","2"
"R5","10k","Resistor_SMD:R_0402_1005Metric","0402WGF1002TCE","C25744","1"
"R6,R7","5.1k","Resistor_SMD:R_0402_1005Metric","0402WGF5101TCE","C25905","2"
"R8,R9,R10,R11,R12,R13,R14,R15,R16,R17,R18,R19,R20,R21,R22,R23","100R","Resistor_SMD:R_0402_1005Metric","0402WGF1000TCE","C25076","16"
"R24,R28","1M","Resistor_SMD:R_0603_1608Metric","0603WAF1004T5E","C22935","2"
"R25,R26,R29,R30","220k","Resistor_SMD:R_0603_1608Metric","0603WAF2203T5E","C22961","4"
"R27,R31","47R","Resistor_SMD:R_0603_1608Metric","0603WAF470JT5E","C23182","2"
"SW1,SW2","PCM12SMTR","Button_Switch_SMD:SW_SPDT_PCM12","PCM12SMTR","C221841","2"
"SW3","BOOTSEL","Button_Switch_SMD:SW_SPST_PTS810","PTS810SJM250SMTRLFS","C116501","1"
"SW4","RESET","Button_Switch_SMD:SW_SPST_PTS810","PTS810SJM250SMTRLFS","C116501","1"
"U1","RP2040","Package_DFN_QFN:QFN-56-1EP_7x7mm_P0.4mm_EP3.2x3.2mm_ThermalVias","RP2040","C2040","1"
"U2","W25Q128JVSIQ","Package_SO:SOIC-8_5.3x5.3mm_P1.27mm","W25Q128JVSIQ","C97521","1"
"U3","USBLC6-2SC6","Package_TO_SOT_SMD:SOT-23-6","USBLC6-2SC6","C7519","1"
"U4","AP2112K-3.3","Package_TO_SOT_SMD:SOT-23-5","AP2112K-3.3TRG1","C51118","1"
"U5,U8","SN74LVC245APWR","Package_SO:TSSOP-20_4.4x6.5mm_P0.65mm","SN74LVC245APWR","C7848","2"
"U6,U7,U9,U10","USBLC6-4SC6","Package_TO_SOT_SMD:SOT-23-6","USBLC6-4SC6","C111212","4"
"U11,U12","TLV9061IDBVR","Package_TO_SOT_SMD:SOT-23-5","TLV9061IDBVR","C398358","2"
"Y1","12MHz","Crystal:Crystal_SMD_3225-4Pin_3.2x2.5mm","ABM8-272-T3","C20625731","1"
